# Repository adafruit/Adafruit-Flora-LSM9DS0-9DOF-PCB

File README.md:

# Adafruit Flora LSM9DS0 9DOF PCB
<a href="http://www.adafruit.com/products/2020"><br/>
Click here to purchase one from the Adafruit shop</a>

Add motion, direction and orientation sensing to your wearable FLORA project with this high precision 9-DOF sensors. Inside are three sensors, one is a classic 3-axis accelerometer, which can tell you which direction is down towards the Earth (by measuring gravity) or how fast the board is accelerating in 3D space. The other is a 3-axis magnetometer that can sense where the strongest magnetic force is coming from, generally used to detect magnetic north.  The third is a 3-axis gyroscope that can measure spin and twist.  By combining this data you can REALLY orient yourself.

When we saw the new LSM9DS0 from ST micro we thought - wow this could really make some wearables super smart. Design your own activity or motion tracker with all the data! The sensor has a digital (I2C) interface. Attaching it to the FLORA is simple: line up the sensor so its adjacent to the SDA/SCL pins and sew conductive thread from the 3V, SDA, SCL and GND pins. They line up perfectly so you will not have any crossed lines. You can only connect one of these sensors to your FLORA, but you can connect other I2C sensors/outputs by using the set of SCL/SDA pins on the opposite side.

PCB files for Adafruit Flora LSM9DS0 9-DOF Sensor PCB. The format is EagleCAD schematic and board layout
- https://www.adafruit.com/product/2020

### License

Adafruit invests time and resources providing this open source design, please support Adafruit and open-source hardware by purchasing products from [Adafruit](https://www.adafruit.com)!

All text above must be included in any redistribution

Designed by Limor Fried/Ladyada for Adafruit Industries.
Creative Commons Attribution/Share-Alike, all text above must be included in any redistribution. 
See license.txt for additional information.

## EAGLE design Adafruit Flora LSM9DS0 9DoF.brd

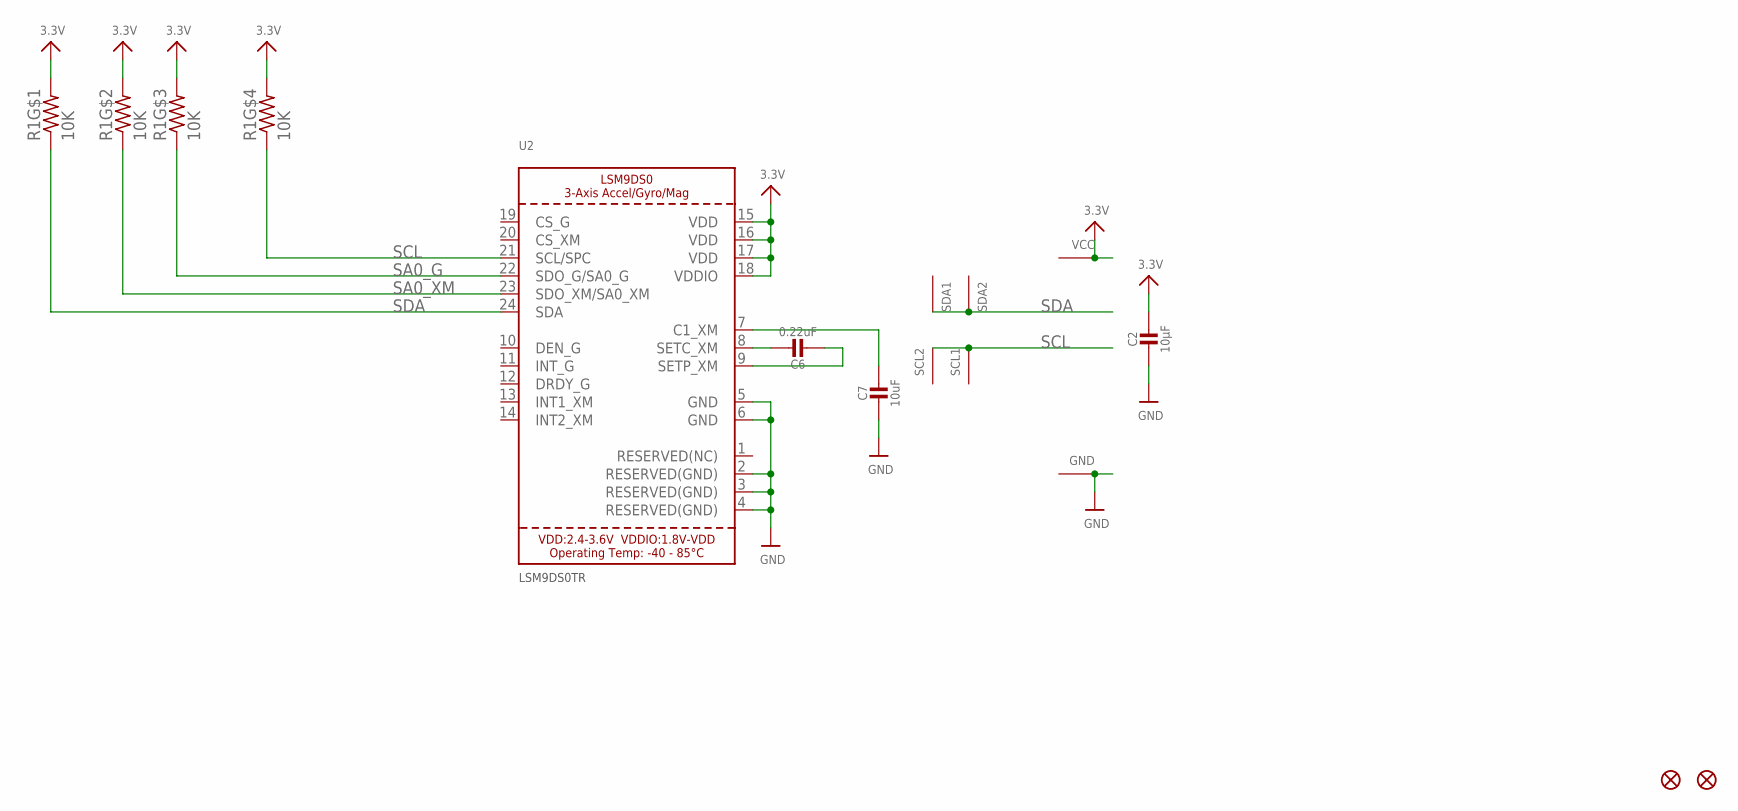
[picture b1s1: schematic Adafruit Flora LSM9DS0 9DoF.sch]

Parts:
C2: 10µF; 0805_10MGAP
C6: 0.22uF; 0805-NO
C7: 10uF; 0805-NO
FID1, FID2: FIDUCIAL""; FIDUCIAL_1MM
GND: SEWTAP0.5IN; SEWINGTAP_0.5
R1: 10K; RESPACK_4X0603
SCL1, SCL2: SEWTAP0.5IN; SEWINGTAP_0.5
SDA1, SDA2: SEWTAP0.5IN; SEWINGTAP_0.5
U2: LSM9DS0TR; LGA24_4X4MM
VCC: SEWTAP0.5IN; SEWINGTAP_0.5

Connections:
3.3V: C2.1, R1.5 (2), R1.6 (2), R1.7 (2), R1.8 (2), U2.15 (VDD), U2.16 (VDD), U2.17 (VDD), U2.18 (VDDIO), VCC.TAP
GND: C2.2, C7.2, GND.TAP, U2.2 (RESERVED(GND)), U2.3 (RESERVED(GND)), U2.4 (RESERVED(GND)), U2.5 (GND), U2.6 (GND)
unnamed: C6.1, U2.8 (SETC_XM)
unnamed: C6.2, U2.9 (SETP_XM)
unnamed: C7.1, U2.7 (C1_XM)
SA0_G: R1.3 (1), U2.22 (SDO_G/SA0_G)
SA0_XM: R1.2 (1), U2.23 (SDO_XM/SA0_XM)
SCL: R1.4 (1), SCL1.TAP, SCL2.TAP, U2.21 (SCL/SPC)
SDA: R1.1, SDA1.TAP, SDA2.TAP, U2.24 (SDA)

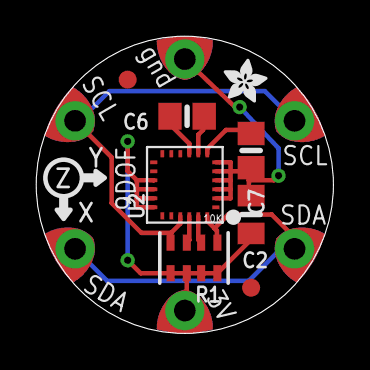
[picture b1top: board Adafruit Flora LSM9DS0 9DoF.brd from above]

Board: 2 copper layers, 16.5 x 16.5 mm, 14 parts (0 on the bottom side), 9 nets.

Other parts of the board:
U$4: ADAFRUIT_2.5MM

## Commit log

2015-06-22 init

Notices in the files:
parts and their libraries:
microbuilder: This work is placed in the public domain, and may be freely used for commercial and non-commercial work with the following conditions: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
